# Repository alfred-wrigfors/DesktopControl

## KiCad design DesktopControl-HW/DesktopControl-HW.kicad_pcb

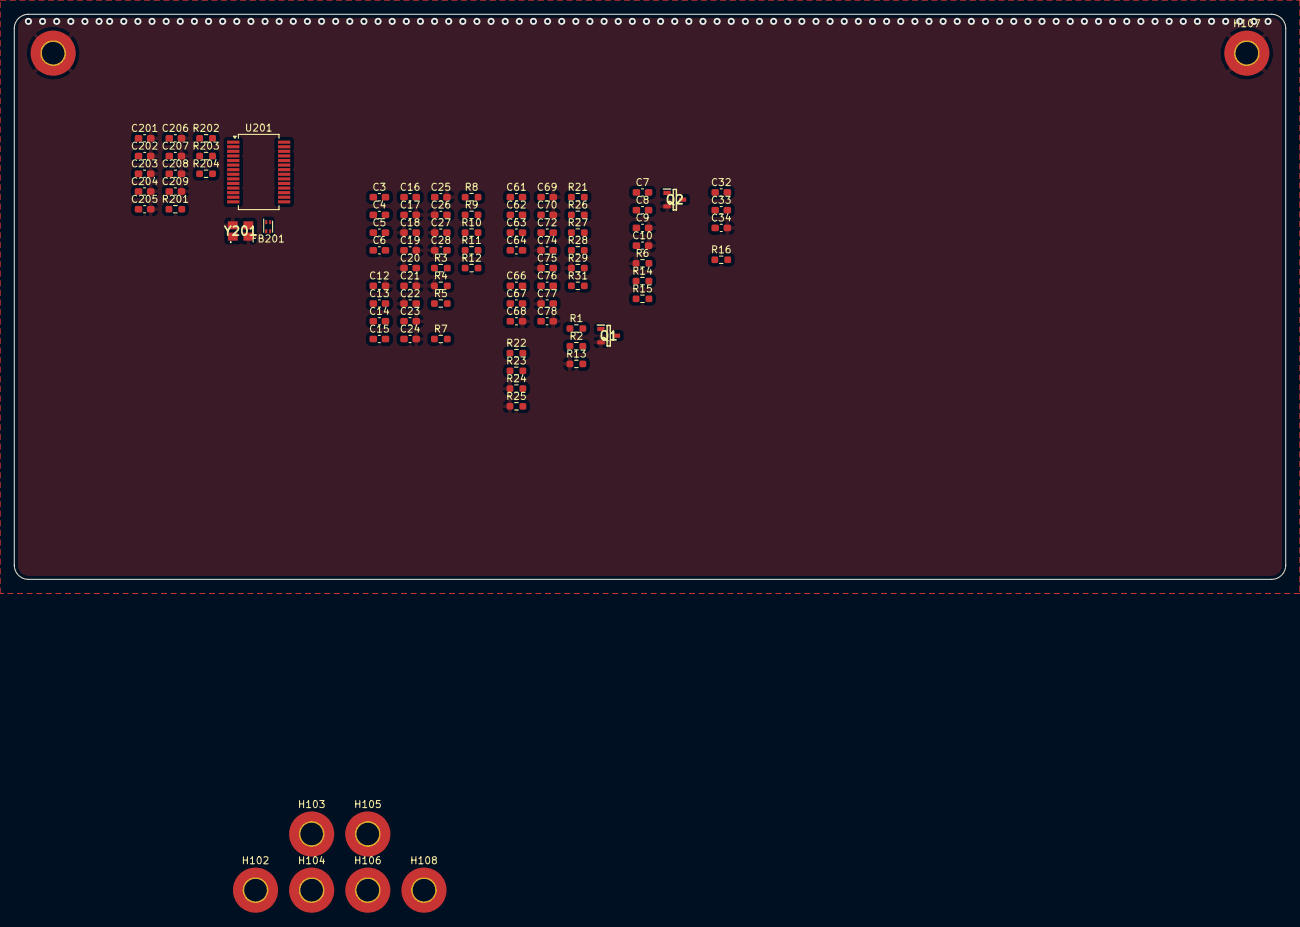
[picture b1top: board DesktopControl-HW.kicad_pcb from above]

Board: 4 copper layers, 180.0 x 80.0 mm, 95 parts (0 on the bottom side), 42 nets, no tracks yet.

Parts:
C3, C4, C61, C62: 100n; C_0603_1608Metric_Pad1.08x0.95mm_HandSolder
C5, C6, C19, C20, C23, C28, C63, C64: 1n; C_0603_1608Metric_Pad1.08x0.95mm_HandSolder
C7, C8, C9, C10, C32, C33, C34, C68, C77, C78: 1u; C_0603_1608Metric_Pad1.08x0.95mm_HandSolder
C12, C201, C202, C203, C204, C205, C206, C207, C208, C209: C; C_0603_1608Metric_Pad1.08x0.95mm_HandSolder
C13, C14, C15, C16, C66, C67, C72, C76: 220n; C_0603_1608Metric_Pad1.08x0.95mm_HandSolder
C17, C18, C24, C26, C69, C74: 680n; C_0603_1608Metric_Pad1.08x0.95mm_HandSolder
C21, C22, C25, C27, C70, C75: 10n; C_0603_1608Metric_Pad1.08x0.95mm_HandSolder
FB201: FerriteBead; L_CommonModeChoke_Coilcraft_0603USB
H101, H102, H103, H104, H105, H106, H107, H108: MountingHole_Pad; MountingHole_3.2mm_M3_Pad_TopBottom
Q1, Q2: PMV280ENEAR; SOT95P230X110-3N
R1, R15, R31: 100k; R_0603_1608Metric_Pad0.98x0.95mm_HandSolder
R2, R5, R6, R13, R14, R16: 10k; R_0603_1608Metric_Pad0.98x0.95mm_HandSolder
R3, R11, R12, R24, R25, R26: 47k; R_0603_1608Metric_Pad0.98x0.95mm_HandSolder
R4: 5k6; R_0603_1608Metric_Pad0.98x0.95mm_HandSolder
R7, R8, R9, R10, R21, R27: 3R3; R_0603_1608Metric_Pad0.98x0.95mm_HandSolder
R22, R23: 12k; R_0603_1608Metric_Pad0.98x0.95mm_HandSolder
R28, R29: 51k; R_0603_1608Metric_Pad0.98x0.95mm_HandSolder
R201, R202: 22R; R_0603_1608Metric_Pad0.98x0.95mm_HandSolder
R203: 1k5; R_0603_1608Metric_Pad0.98x0.95mm_HandSolder
R204: 1M; R_0603_1608Metric_Pad0.98x0.95mm_HandSolder
U201: PCM2902; SSOP-28_5.3x10.2mm_P0.65mm
Y201: LFXTAL035264

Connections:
+15V: C3.1, C4.1, C5.1, C6.1, C61.1, C62.1, C63.1, C64.1, R2.2, R14.2
/AMPLIFIER/GAIN/SLV: R3.1, R4.2
/AMPLIFIER/GVDD: C12.1, R3.2, R5.2
/AMPLIFIER/MUTE: Q1.3 (D), Q2.3 (D), R1.2, R2.1, R6.2, R13.2, R14.1, R15.2
/AMPLIFIER/OUT_LN: C26.2, C28.2, R10.1, R12.1
/AMPLIFIER/OUT_LP: C23.1, C24.1, R9.2, R12.2
/AMPLIFIER/OUT_RN: C18.2, C20.2, R8.1, R11.1
/AMPLIFIER/OUT_RP: C17.1, C19.1, R7.2, R11.2
/AMPLIFIER_SUB/AUDIO_L: C32.1, R22.2
/AMPLIFIER_SUB/AUDIO_R: C33.1, R23.2
/AMPLIFIER_SUB/GAIN/SLV: R28.1, R29.2
/AMPLIFIER_SUB/GVDD: C78.1, R28.2, R31.2
/AMPLIFIER_SUB/LINP: C32.2, C33.2
/AMPLIFIER_SUB/OUTN: C66.2, C76.2
/AMPLIFIER_SUB/OUTP: C67.2, C72.2
/AMPLIFIER_SUB/OUT_N: C74.2, C77.2, R26.1, R27.1
/AMPLIFIER_SUB/OUT_P: C68.1, C69.1, R21.2, R26.2
/AUDIO_L: C8.1, R22.1, R25.2
/AUDIO_R: C7.1, R23.1, R24.2
/CODEC/CODEC_3V3: C205.1, R203.2, U201.8 (SEL0), U201.9 (SEL1), U201.27 (VDDI), U201.28 (~SSPND)
/CODEC/USB_DP: R201.1, R203.1
/CODEC/VBUS_F: C204.1, FB201.2, U201.3 (VBUS)
/CODEC/XTI: C202.1, R204.2, U201.21 (XTI), Y201.3
/CODEC/XTO: C203.1, R204.1, U201.20 (XTO), Y201.1
GND: C9.2, C10.2, C12.2, C17.2, C18.1, C19.2, C20.1, C21.2, C22.1, C23.2, C24.2, C25.2, C26.1, C27.1, C28.1, C34.2, C68.2, C69.2, C70.2, C74.1, C75.1, C77.1, C78.2, C201.2, C202.2, C203.2, C204.2, C205.2, C206.2, C207.2, C208.2, C209.2, H101.1, H102.1, H103.1, H104.1, H105.1, H106.1, H107.1, H108.1, Q1.2 (S), Q2.2 (S), R4.1, R6.1, R13.1, R24.1, R25.1, R29.1, U201.4 (DGNDU), U201.11 (AGNDC), U201.18 (AGNDP), U201.22 (AGNDX), U201.26 (DGND), Y201.2, Y201.4
unnamed: C3.2, C4.2, C5.2, C6.2
unnamed: C21.1, R7.1
unnamed: C22.2, R8.2
unnamed: C25.1, R9.1
unnamed: C27.2, R10.2
unnamed: C61.2, C62.2, C63.2, C64.2
unnamed: C70.1, R21.1
unnamed: C75.2, R27.2
unnamed: Q1.1 (G), R1.1
unnamed: Q2.1 (G), R15.1
unnamed: R201.2, U201.1 (D+)
unnamed: R202.2, U201.2 (D-)
unnamed: C209.1, U201.10 (VCCCI)
unnamed: C207.1, U201.17 (VCCP1I)
unnamed: C206.1, U201.19 (VCCP2I)
unnamed: C201.1, U201.23 (VCCXI)
unnamed: C208.1, U201.14 (VCOM)

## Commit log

2025-03-04 Added KiCAD files
2025-03-04 Beginning of HW
2025-05-26 Rework amplifier configuration, add amplifier for subwoofer and start check of codec
